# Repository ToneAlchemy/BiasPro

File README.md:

# 🎛️ Arduino Tube Amp BiasPro

This repository contains the complete, mathematically hardened firmware for a professional-grade, dual-probe vacuum tube BiasPro. Designed for guitar amplifier technicians, this tool provides real-time, high-resolution measurements of Plate Voltage, Cathode Current, and True Plate Dissipation (Watts & %) for power tubes (e.g., 6L6GC, EL34, 6V6, KT88).

This firmware was completely re-architected from scratch using modern, memory-safe embedded C++ principles to eliminate dynamic memory leaks and ensure rock-solid physical safety lockouts.

> **Current firmware version: v1.1.1** — see [CHANGE_LOG.md](CHANGE_LOG.md) for the full change history. Highlights since v1.0.0: a **vertically stacked, horizontally centered layout on the Tube Select and Profile Manager screens** (with improved line spacing for clear reading), a **Hold LEFT shortcut** to escape the Profile Manager directly to Tube Select, a **live plate-voltage readout on the Calibration screen** (match it to your DMM as you adjust), **sensor-glitch rejection** so a noisy ADC read can't false-release the lockout or flash 0 V, **profile-store protection** so a bad edit can't wipe your saved tube profiles, and a **flicker-free VOLTAGE LOCKOUT screen**.

| **1. Splash Screen** | **2. Tube Select** | **3. Live Bias Mode** |
| :---: | :---: | :---: |
|  |  |  |
| **4.  Calibration** | **5. Profiles Manager** | **6. Profile Edit** |
|  |  |  |
| **7. EDIT PROFILE** | **8. BiasPro Enclosure** | **9. BiasPro - Setup** |
|  |  |  |

---

## ⚠️ High-Voltage Safety Warning
**LETHAL VOLTAGES ARE PRESENT IN TUBE AMPLIFIERS.**

Tube amplifiers store lethal voltages in their filter capacitors even after being unplugged. This firmware is only a measurement tool; it **cannot** make unsafe wiring or handling safe. 
* Never connect the USB port to a computer while the probes are plugged into a live amplifier. 
* Always use a dummy load or speaker cabinet.
* If you are not trained in high-voltage safety, take your amplifier to a qualified technician. Build and use this project entirely at your own risk.

---

> [!CAUTION]
> ## ⚠️ WARNING: HIGH VOLTAGE SAFETY
>
> **Tube amplifiers contain lethal high voltage (often 400V–500V+), even when powered off and unplugged.**
>
> This project involves building and using test equipment that interfaces directly with these dangerous circuits.
> * **Risk of Death:** Incorrect wiring of the bias probes or misuse of this device can expose you to lethal current.
> * **Filter Capacitors:** High voltage can remain stored in the amplifier's capacitors long after the power is cut. You must know how to safely drain filter capacitors before opening any chassis.
> * **Qualified Personnel Only:** If you are not trained in high-voltage safety or are uncomfortable working with live circuits, **do not build or use this device**. Take your amplifier to a qualified technician instead.
>
> **DISCLAIMER & NO SUPPORT:** This project is provided "as is" with **no warranty and no technical support**. The author cannot provide assistance with assembly, troubleshooting, or code modifications. The author assumes no liability for injury, death, or equipment damage resulting from the use or construction of this device. **Use entirely at your own risk.**

> [!IMPORTANT]
> ### ⚡ Critical Safety: Capacitor Discharge
> Before touching any internal component or connecting probes to a chassis, you must verify the filter capacitors are drained.
>
> * **The Golden Rule:** Always measure with a multimeter to confirm 0VDC before touching anything.
> * **Discharge Tool:** Do not rely on the amp to drain itself. Use a dedicated **Capacitor Discharge Tool** to safely bleed off voltage.
>      * *DIY Tip:* You can build one using a high-wattage resistor (e.g., **2kΩ to 5kΩ, 5 Watts**) wired to a probe and an alligator clip for ground. This slows the discharge **and** prevents sparking, unlike a screwdriver short.
> * **One-Hand Rule:** When working on live amps, keep one hand in your pocket to prevent current from passing across your chest/heart.

> [!NOTE]
> ### 🛡️ Recommended Safety Gear
> If you are working inside a live amplifier chassis, we strongly recommend using the following safety equipment:
> 
> * **Isolation Transformer:** This isolates the amplifier from the mains earth ground, significantly reducing the risk of lethal shock if you accidentally touch a live component while grounded.
> * **Dim Bulb Limiter (Current Limiter):** Essential when powering up an amplifier for the first time after a repair. It prevents catastrophic damage (blown transformers) if there is a short circuit.
>      * **⚠️ CRITICAL WARNING:** Do **NOT** attempt to set the final bias while running through a Dim Bulb Limiter. The limiter drops the wall voltage, which lowers the plate voltage and gives false low bias readings. Always bypass the limiter for the final precision bias adjustment.
> * **Variac (Variable Transformer):** Highly recommended for two purposes:
>      1.  **Voltage Stabilization:** Wall voltage fluctuates. A Variac allows you to set the input voltage exactly to your country's standard (e.g., 240V in Australia, 120V in USA, 230V in UK). This ensures your bias readings are accurate and consistent, rather than drifting with high/low wall voltage.
>      2.  **Soft Start / Reforming:** Useful for slowly bringing up the voltage on vintage amplifiers to reform old capacitors safely.

> [!TIP]
> **New to Biasing?** Check out our dedicated guide:
> ### 📖 [Read the Step-by-Step Biasing Guide](BIASING_GUIDE.md)
> *Learn how to safely bias Fender Prosonic & Fixed-Bias Amps.*

---

## ⚙️ Hardware Specifications

* **MCU:** Arduino Nano / ATmega328P
* **Display:** 1.8" 128×160 ST7735/ST7735S SPI TFT (Adafruit PID 358 or compatible generic clone; see [Display Selection & Compatibility Guide](#18-tft-display-selection--compatibility-guide) below)
* **ADC:** ADS1115 (16-bit) at I2C address `0x48`
* **Inputs:** Three tactile switches (Left, Right, Center)

### Immutable Pin Map
| Function | Arduino Nano Pin |
| :--- | :--- |
| **TFT SCLK/SCL** | D13 |
| **TFT MOSI/SDA** | D11 |
| **TFT CS** | D10 |
| **TFT DC** | D9 |
| **TFT RST** | D8 |
| **Button Center** | D7 (Uses `INPUT_PULLUP`) |
| **Button Right** | D6 (Uses `INPUT_PULLUP`) |
| **Button Left** | D5 (Uses `INPUT_PULLUP`) |
| **ADS1115 SDA** | A4 |
| **ADS1115 SCL** | A5 |

### 🖥️ 1.8" TFT Display Selection & Compatibility Guide

When sourcing displays for BiasPro, you will encounter two primary hardware paths: the official Adafruit breakout or generic clone modules. Understanding their electrical architecture is essential for proper wiring and long display life:

| Feature | Adafruit 1.8" TFT Breakout (PID 358) | Generic Clone Module (`Driver IC: ST7735S` / `NOMEN_TEC`) |
| :--- | :--- | :--- |
| **Driver IC** | **ST7735R** | Usually **ST7735S** |
| **Onboard 3.3V LDO Regulator** | ✅ Yes (ultra-low-dropout 3.3V regulator) | ⚠️ **Usually present (`662K`), but verify `U1` & `J1`** |
| **Onboard Logic Level Shifter** | ✅ Yes (active CD74HC4050 buffer IC) | ❌ **None** (pins route straight to glass ribbon) |
| **5V Supply Compatibility** | ✅ Yes (accepts 3.3V – 5V on `VCC`) | ✅ Yes (if `U1` is populated and `J1` is open) |
| **5V Logic Compatibility** | ✅ Native 5V plug-and-play | ⚠️ **Requires 1kΩ to 1.5kΩ series resistors on SPI/control lines** |
| **Header Pin Labels** | `LITE, MISO, SCK, MOSI, TFT_CS, CARD_CS, D/C, RESET, VCC, Gnd` | `GND, VCC/VDD, SCL, SDA, RES/RST, DC, CS, BL/BLK` |

> [!NOTE]
> **Important Distinction on Adafruit PID 358 vs. PID 618:**  
> The official recommended reference part is the **Adafruit PID 358** assembled breakout (which includes the mounting PCB, microSD slot, 3.3V regulator, and CD74HC4050 level shifter).  
> In contrast, **Adafruit PID 618 is the raw, unmounted 1.8" TFT panel only** (flexible ribbon cable, no PCB). PID 618 is strictly 3.3V-only and requires external regulation and level shifting when paired with a 5V Arduino Nano.

---

#### Board Routing & Configuration Details

The `BiasPro_InputProtection_v3` PCB routes the global **5V** rail directly to Pin 8 (`VCC`) of the display header, and routes digital pins `D8`, `D9`, `D10`, `D11`, and `D13` straight to the display's SPI control lines without inline resistor pads. Review the configuration requirements for your specific display:

##### 1. Official Adafruit Breakout (PID 358) — *Recommended Reference Part*

The reference hardware design targets the **Adafruit PID 358** assembled breakout natively:

* **Power:** Connect `VCC` to Arduino Nano 5V (or 3.3V; the onboard regulator safely handles 3.3V–5V input) and `GND` to Arduino GND.
* **Signals:** Wire directly to the Arduino Nano with **no external resistors required** (the onboard CD74HC4050 buffer translates 5V logic down to 3.3V safely):
  * Nano `D13` → Adafruit `SCK`
  * Nano `D11` → Adafruit `MOSI`
  * Nano `D10` → Adafruit `TFT_CS`
  * Nano `D9`  → Adafruit `D/C`
  * Nano `D8`  → Adafruit `RESET`
* **Backlight:** Connect `LITE` to 3V3 or 5V (or to an Arduino PWM pin if software brightness control is desired).
* **Unused Pins:** `CARD_CS` and `MISO` belong to the onboard microSD card socket and remain unconnected in BiasPro.
* **Firmware Support:** BiasPro’s firmware uses `tft.initR(INITR_18BLACKTAB)` via the `Adafruit_ST7735` library, targeting the PID 358 natively.

---

##### 2. Generic / Chinese Clone Modules (ST7735S)

Budget 8-pin breakout modules (frequently marked *Driver IC: ST7735S* or *NOMEN_TEC V2.0*) run on native 3.3V silicon and lack active logic-level translation buffers.

* **VCC Power Compatibility (`U1` & `J1` Check):**
  * Inspect the rear PCB of the module: most clones include a 3-pin 3.3V LDO regulator marked **`662K`** (or `AMS1117-3.3`) at footprint **`U1`**, alongside an unbridged solder jumper **`J1`**.
  * If `U1` is populated and `J1` is open, feeding 5V into `VCC` is completely safe (the regulator steps 5V down to 3.3V for internal panel power).
  * **Warning:** If `U1` is unpopulated and `J1` is bridged, the module is strictly 3.3V-only. Connecting 5V to `VCC` will destroy the panel.
* **5V Logic Levels & Clamping:**
  * Because generic modules omit active buffer ICs, driving them directly with the Nano's 5V SPI lines forces the ST7735's internal silicon clamping diodes to shunt the excess voltage down to 3.3V.
  * **Intermittent Bench Biasing (Stock Direct Connection):** For standard tube biasing workflows (5 to 15 minutes of bench runtime per amplifier), the direct connection operates reliably without immediate failure.
* **Extended / Continuous Duty Cycles (Recommended Protection):** For long-term reliability and day-long bench operation, insert **1kΩ to 1.5kΩ series resistors** into every digital control line to eliminate clamping stress and keep the display controller cool:
  * Nano `D13` → [1kΩ Resistor] → Display `SCL` / `SCK`
  * Nano `D11` → [1kΩ Resistor] → Display `SDA` / `MOSI`
  * Nano `D10` → [1kΩ Resistor] → Display `CS`
  * Nano `D9`  → [1kΩ Resistor] → Display `DC` / `A0`
  * Nano `D8`  → [1kΩ Resistor] → Display `RES` / `RESET`
* **PCB Assembly Note:** Because the `BiasPro_InputProtection_v3` PCB routes the Nano directly to the display header without inline resistor pads, builders opting for series resistors should wire the clone module off-board or install inline resistors along the wiring harness rather than soldering the display directly flush into the PCB header.
* **Backlight (`BL` / `BLK`):** The onboard transistor (`Q1` / `J3Y`) and base resistor handle switching. Connect `BL` to the Nano's `3V3` pin, or to an Arduino GPIO pin through a 1kΩ resistor if software dimming is desired.

---

## 🛠️ Build & Flash Instructions

### 1. Pinned Dependencies
To guarantee a successful compile, you **must** use these exact library versions in the Arduino IDE:
* `Adafruit GFX Library` v1.12.5
* `Adafruit ST7735 and ST7789 Library` v1.11.0
* `Adafruit BusIO` v1.17.4

### 2. CRITICAL: 99% Flash Memory Limit & Bootloaders
The firmware compiles to approximately **30,626 bytes** of program storage. This is a very tight fit on older hardware, but it will successfully flash to both new and old Arduino Nanos.

* **Newer Arduino Nano (Standard Bootloader):** If you have a newer official Nano or a high-quality modern clone, use the `Processor: ATmega328P` setting in the Arduino IDE. These boards use the modern *Optiboot* bootloader, which leaves 32,256 bytes of usable flash space. The firmware will fit easily with roughly **1.6KB to spare**.

* **Older Arduino Nano & Generic Clones (Old Bootloader):** Many cheaper clones and older Nanos use the legacy bootloader, which takes up more space and leaves exactly 30,720 bytes of usable flash space. The firmware **will still successfully flash** using the `Processor: ATmega328P (Old Bootloader)` setting, fitting with roughly **94 bytes to spare**:
  ```text
  Sketch uses 30626 bytes (99%) of program storage space. Maximum is 30720 bytes.
  Global variables use 750 bytes (36%) of dynamic memory, leaving 1298 bytes for local variables. Maximum is 2048 bytes.
  ```
  It works perfectly, but you have very little room to add additional features or text without overflowing the memory.

* **Need more space on an old Nano?** You can manually upgrade an old Nano to the modern *Optiboot* bootloader using an ISP programmer. Once upgraded, you simply change your board selection in the Arduino IDE to **"Arduino Uno"** to unlock the extra 1.5KB of flash space.

### 3. EMI & I2C Freeze Protection
Tube amplifiers are electrically noisy environments. High voltage spikes, flyback EMF, or loose tube socket connections can create strong Electromagnetic Interference (EMI) that can lock up the internal I2C bus connecting the Arduino to the ADS1115 ADC.

To protect against these EMP-like events, this firmware completely bypasses the standard Adafruit ADC library and manually writes to the I2C registers. More importantly, it utilizes the modern `Wire.setWireTimeout(25000, true)` feature. 

* **How it works:** If the I2C bus freezes due to interference, the system detects the hang within 25 milliseconds, automatically resets the I2C hardware pins, and immediately resumes reading the Bias probes without ever rebooting the Arduino or losing your place on the screen.

* **Why no Hardware Watchdog Timer (WDT)?** Older versions of this project used the hardware WDT. However, a severe silicon bug in common LGT8F328P Arduino Nano clones caused the WDT to trigger infinite boot-loop crashes during UI updates. The software-level `Wire` timeout is infinitely more reliable, handles EMI elegantly, and completely avoids these bootloader bugs.

#### Hardware I²C Pull-Up Reinforcement (EMI Hardening)
In addition to the software timeout recovery, the physical BiasPro hardware reinforces the ADS1115 I²C bus with auxiliary pull-up resistors:
* **`SDA` $\rightarrow$ 4.7kΩ $\rightarrow$ `VDD`**
* **`SCL` $\rightarrow$ 4.7kΩ $\rightarrow$ `VDD`**

These $4.7\text{ k}\Omega$ metal-film resistors were added during live amplifier testing to strengthen the I²C bus against EMI-induced corruption and bus lockups in electrically aggressive valve-amplifier environments. By lowering the bus impedance and sharpening the $SDA$/$SCL$ rising edges, the bus becomes significantly more immune to capacitively coupled noise from high-voltage plate leads and transformer fields.

Many common ADS1115 breakout modules already include $10\text{ k}\Omega$ onboard pull-up resistors. Adding external $4.7\text{ k}\Omega$ resistors places them in parallel, resulting in an effective bus pull-up impedance of approximately $\approx 3.2\text{ k}\Omega$ (drawing only $\approx 1.56\text{ mA}$ sink current at 5V, comfortably within the $3\text{ mA}$ I²C standard limit). These hardware pull-ups work synergistically with the firmware’s `Wire.setWireTimeout` mechanism to deliver rock-solid stability.

---

## ⚠️ Troubleshooting

### 1. Upload Failed? (stk500 Error)
If you are unable to upload the firmware and see an error like `stk500_recv(): programmer is not responding`:

* **The Cause:** You are likely using an older Arduino Nano (or a generic clone) that uses the legacy bootloader.

* **The Fix:** In the Arduino IDE, go to **Tools > Processor** and change the setting from "ATmega328P" to **"ATmega328P (Old Bootloader)"**. Then try uploading again.
* *Note:* Newer official Nanos (and USB-C versions) usually use the standard "ATmega328P" setting.

### 2. The "Boot Loop" Issue (Legacy Hardware)
Some older Arduino Nano boards (and many low-cost clones) came with an outdated "Bootloader" that had a bug preventing the chip from recovering correctly after a hardware Watchdog Reset. 

* **The Fix:** This has been permanently fixed in this modern codebase! We completely stripped out the hardware Watchdog Timer and replaced it with a targeted `Wire.setWireTimeout` bus reset. You should no longer experience infinite boot loops when encountering EMI. If you do, ensure you have correctly installed the `Wire` library updates in the Arduino IDE.

### 3. Adafruit Display Clones ST7735 1.8" TFT - White Screen / Static / Wrong Colors?
If your display lights up but shows static, garbage pixels, or wrong colors:

* **The Cause:** You likely have a "Green Tab" or "Red Tab" clone display. The plastic tab on the screen protector often indicates the internal driver version.

* **The Fix:** Open the firmware source code (`DisplayManager.cpp` or main `.ino` configuration) and find the initialization line: `tft.initR(INITR_18BLACKTAB);` 
Change it to one of the following and re-upload until the screen looks correct:
  * `tft.initR(INITR_18GREENTAB);`
  * `tft.initR(INITR_18REDTAB);`

### 4. Arduino Nano "L" LED Flickering Constantly?
If you notice the onboard yellow/orange **`L`** LED on your Arduino Nano flickering continuously while the device is running:

* **This is completely normal and indicates healthy operation.**
* On the Arduino Nano hardware, the onboard `L` LED is hardwired directly to digital pin **`D13`**.
* In BiasPro, `D13` serves as the high-speed SPI Clock (`TftSclkPin`). Every time the live bias values update (multiple times per second), thousands of SPI clock pulses toggle D13 at high frequency.
* The flickering `L` LED effectively functions as a live hardware activity monitor showing active SPI communication between the ATmega328P and the display.

---

## 💻 Software & Development Environment

This project is written as a standard Arduino sketch (`.ino`) and was developed using the official **Arduino IDE**.

* **Recommended Method:** We strongly recommend using the **Arduino IDE** for the easiest setup. Its built-in *Library Manager* (Tools > Manage Libraries) makes it simple to install the required dependencies (e.g., Adafruit GFX) without complex manual configuration.

* **Alternative IDEs:** Advanced users can compile this code in other environments, such as **Visual Studio Code (with PlatformIO)** or **Microchip Studio**. However, please note that you will need to manually manage library paths and dependencies.
* **📥 Download Official Arduino IDE:** [Download Official Arduino IDE](https://www.arduino.cc/en/software)

---

## 🧪 Tests

The pure calculation and storage logic (bias math, probe classification, EEPROM
checksums/validation, and the over-voltage protection state machine) lives in
Arduino-independent units (`MathCalculations`, `ProtectionSystem`, `StorageCore`)
so it can be verified on a PC with any C++17 compiler — no board required. The
host tests link the **actual firmware sources**, not a copy, so they cannot drift
from what ships.

```bash
# From the repository root, with g++ (or clang++):
g++ -std=c++17 -I BiasPro test/host_calculation_tests.cpp \
    BiasPro/MathCalculations.cpp BiasPro/ProtectionSystem.cpp \
    BiasPro/StorageCore.cpp -o biaspro_host_tests
./biaspro_host_tests        # expect: "host calculation tests passed"
```

A second, source-level UI regression check (PowerShell) asserts that the display
code keeps using its incremental-redraw pattern and that the safety-screen
routing stays intact:

```powershell
powershell -ExecutionPolicy Bypass -File test/screen_redraw_static_check.ps1
```

---

## Features

BiasPro introduces professional-grade data integrity and safety features not found in standard DIY alternatives.

### 🛠 Core Functionality
* **Dual Probe Measurement:** Simultaneous real-time monitoring of Tube A and Tube B.

* **True Plate Dissipation:** Calculates power (Watts) and dissipation percentage based on the specific tube type.

* **Screen Current Correction:** Implements industry-standard math to subtract estimated screen current, ensuring the displayed bias represents true *Plate* dissipation, not just Cathode current.

### 💾 Robust Data Integrity
* **Checksum Protection:** The EEPROM data includes a computed checksum. If the memory is corrupted or a new chip is installed, the system detects the error and automatically restores safe default values, preventing dangerous behavior.

* **Safety Clamps:** The Calibration Menu now prevents users from accidentally setting dangerous values (e.g., setting a shunt resistor to 0.0Ω or a voltage scaler to 0), effectively "clamping" entries to safe, realistic ranges.

* **Profile Store Protection:** Your custom tube profiles are validated on both save and load. A malformed entry (for example a blank name) is rejected rather than written, so a bad edit can never silently wipe your saved profiles back to defaults on the next power-up.

### 🛡️ Safety & Reliability
* **Active Over-Voltage Monitor:** While in **Live Bias mode**, the plate voltage is checked on every measurement cycle; if it exceeds the configured limit the interface locks and displays a red "LOCKOUT" warning until the voltage falls back into the safe band. (The lock, once tripped, persists across screens until released.) **This automatic check runs only in Live Bias mode — it is _not_ active on the Calibration screen**, even though that screen shows a live voltage. During calibration, rely on your DMM and your own judgement (see the Calibration Guide warning below).

* **Safety Hysteresis:** The system requires a voltage drop of 50V (hysteresis) before resetting the safety lock, preventing rapid toggling near the limit.

* **Input Debouncing:** Advanced state-machine logic eliminates switch "recoil" and bounce, ensuring the cursor never jumps unintentionally.

* **Sensor-Glitch Rejection:** A failed or corrupted ADC read (for example from an EMI burst) is flagged invalid rather than trusted. An invalid reading can **never** release an active voltage lockout, and Live Bias mode holds the last good measurement instead of momentarily flashing 0 V.

* **Flicker-Free Display:** Every screen — including the red VOLTAGE LOCKOUT alert — uses incremental redraw, so critical readouts stay rock-steady instead of strobing.

* **Centered, Stacked UI Layout:** Selection screens (Tube Select and Profile Manager) feature vertically stacked, horizontally centered text elements with balanced line spacing for improved readability.

### ⚙️ On-Board Calibration
* **Software Calibration:** Shunt resistance and Voltage Divider scaling can be adjusted via the screen menu and saved to EEPROM. You do not need to edit the source code to calibrate the unit. Edits save **automatically** when you advance to the next field or leave the screen — there is no separate "save" step — which also minimises wear on the EEPROM.

* **Live Voltage Feedback:** While adjusting the Scale or Shunt fields in Calibration mode, the screen displays a live, non-blocking computed plate voltage (refreshed every ~350 ms) for the active probe. This allows you to match the calibration to your DMM readings in real time.

---

## 🧠 How It Works (Theory of Operation)

For those interested in the engineering, here is how the BiasPro safely measures high-voltage tube amplifiers.

### 1. Measuring Plate Voltage (The Voltage Divider)
The Arduino cannot measure 500V directly, and the ADS1115 is configured with a high-resolution Programmable Gain Amplifier (PGA) range of ±0.256V (256 mV) to maximize measurement accuracy.
* **The Circuit:** Inside the probe, a **Voltage Divider** network (1MΩ high-side, 100Ω low-side) scales the high voltage down to a safe millivolt range (0-256 mV).
* **The Math:** The device measures this low millivolt reading and multiplies it by the **Voltage Scale Factor** (defaults to 10.00, calibrated in software) to calculate the true High Voltage.
    * *Example:* 450V from the amp is stepped down by the 10,001:1 divider to approximately 45mV (0.045V) at the ADC input. The firmware multiplies this 45mV reading by the Scale Factor (10.00) to display "450V" on the screen.

### 2. Measuring Bias Current (The Shunt Resistor)
To measure current, we use **Ohm's Law** (`V = I × R`).
* **The Circuit:** The tube's cathode current flows through a precision **1Ω Shunt Resistor** to ground.

* **The Measurement:** The current flowing through the resistor creates a tiny voltage drop across it (e.g., 35mA of current creates 35mV).

* **The ADC:** The high-precision **ADS1115 ADC** measures this tiny voltage drop with extreme accuracy. The Arduino then converts that millivolt reading directly into milliamps (since 1mV = 1mA across a 1Ω resistor).

### 3. Calculating Dissipation (The Wattage)
Once the system knows the Voltage (V) and the Current (I), it calculates the Plate Dissipation in real-time.

* **Formula:** `Watts = Plate Voltage × Plate Current`

* **Screen Correction:** If enabled, the system first subtracts the estimated Screen Current from the total current to ensure the Wattage displayed is for the **Plate only**, providing the most accurate bias reading possible.

---

## Bill of Materials (BOM)

| Quantity | Component | Description |
| :------- | :--- | :--- |
| 1 | Arduino Nano (Recommended: USB-C Version) | Microcontroller board (ATmega328P) |
| 1 | Adafruit ST7735 1.8" TFT | 160x128 Color TFT Display (SPI) |
| 1 | ADS1115 16-Bit ADC Module | High-precision 4-channel ADC (I2C) |
| 3 | Tactile Push Buttons | Menu navigation (Left, Right, Center/Select) |
| 1 | Project Enclosure | 3D printed case (See below) |
| - | Hook-up Wire | 22 AWG for internals |
| 2 | Bias Probes | Octal (8-pin) probes (e.g., TubeDepot Bias Scout or DIY) |

* **Download Link:** [Bill of Materials (BOM) for the BiasPro.txt](./HARDWARE%20-%20PCB%20KICAD/Bill%20of%20Materials%20(BOM)%20for%20the%20BiasPro.txt)

---

## 🛑 Hardware Compatibility & Critical Warnings

Before sourcing parts, please review these critical hardware constraints to ensure your build works correctly.

### 1. ADC Module: ADS1115 Only (No ADS1015)

* **⚠️ CRITICAL:** You **MUST** use the **ADS1115 (16-Bit)** ADC module.

* **Do NOT use the ADS1015:** This is a cheaper, 12-bit version that looks identical.

* **The Issue:** The firmware uses a specific multiplier (`0.0078125 mV/bit`) calculated for 16-bit resolution. If you use an ADS1015, your bias readings will be incorrect by a factor of 16.

### 2. Display: ST7735 TFT Only (No OLEDs)

* **Required:** Adafruit **ST7735 1.8" Color TFT** (or compatible).

* **Not Supported:** This firmware is **NOT** compatible with monochrome OLED displays (SSD1306 or SH1106) used in other versions.

### 3. Arduino Nano Bootloader

* **Recommendation:** We recommend buying an Arduino Nano with the modern **Optiboot** bootloader (often found on USB-C versions) as it provides more flash memory and overall better stability.

### 4. Power Source (No Heater Power)
* **Supported:** Isolated USB Wall Charger or 9V Battery.

* **Not Supported:** Do **NOT** attempt to power this unit directly from the amplifier's 6.3V AC heater lines.

* **The Risk:** This hardware revision does not include the necessary rectification circuitry. Connecting heater lines to the Arduino will destroy the unit.

### 5. Isolation Transformers & USB

* **Clarification:** Even if you plug the amplifier into an **Isolation Transformer**, it is **STILL UNSAFE** to connect the BiasPro's USB port to a computer while probing.

* **The Physics:** Most isolation transformers pass the **Earth Ground** pin straight through. This means the Ground Loop danger persists. **Never connect USB to a PC while the probes are in an amp. If you do so, you do it at your own risk!**

### 🛠️ Building the Probes (Recommended Kit)

We highly recommend the **Tube Depot Bias Scout Kit** for your hardware. It provides a professional, safe, and robust enclosure for the socket and resistor.

* **Product Link:** [Tube Depot Bias Scout Kit](https://www.tubedepot.com/products/tubedepot-bias-scout-kit)

* **Assembly Manual:** [Download PDF Instructions](https://s3.amazonaws.com/tubedepot-com-production/spree/attached_files/td_bias_scout_assy_manual_v3.2.pdf)

**Assembly Notes for this Project:**

1. **The Resistor:** The kit includes a **1Ω 1W resistor**. This is perfect for this project and matches the default calibration (1.00Ω).

2. **Wiring Colors:** If you follow the standard instructions, the output plugs will match this project's wiring guide:
   - **Red:** Plate Voltage (Connect to PCB `V_IN` via voltage divider).
   - **Black:** Ground (Connect to PCB `GND`).
   - **White:** Cathode Current (Connect to PCB `ADC_IN`).

3. **Connection:** You can either cut the banana plugs off and wire them directly to your PCB/Enclosure, or install female banana jacks on your BiasPro enclosure for a detachable probe.

---

## 🔌 DIY Probe Construction & Theory
While we recommend the **Tube Depot Bias Scout Kit** for the easiest assembly, you can build your own probes using the Bias Scout Kit Instructions with standard components.

### 🛠️ DIY Parts List (Per Probe)
To build one probe, you will need:
* **1x Octal Tube Base:** (e.g., P-SP8-47X) - The male plug that goes into the amp.
* **1x Octal PCB Socket:** (e.g., P-ST8-810-PCL) - The female socket the tube plugs into.
* **1x 1Ω Resistor:** (2 Watt or greater, 1% Tolerance) - *Current Shunt*.
* **1x 1MΩ Resistor:** (1/2 Watt or greater, 1% Tolerance) - *Voltage Divider High Side*.
* **1x 100Ω Resistor:** (1/8 Watt or greater, 1% Tolerance) - *Voltage Divider Low Side*.
* **3-Conductor Cabling:** Shielded audio cable or twisted wire.
* **Banana Plugs / Jacks:** To connect to the main unit.
* **Assembly Manual:** [Download PDF Instructions](https://s3.amazonaws.com/tubedepot-com-production/spree/attached_files/td_bias_scout_assy_manual_v3.2.pdf)
  
> [!NOTE]
> The **Hoffman Amps Bias Checker** probe design will **NOT** work with this project. That probe only measures Cathode Current. This project requires probes that measure both Plate Voltage *and* Cathode Current.

---

## 3D Printed Enclosure

A custom enclosure has been designed to house the Arduino Nano, Display, and Buttons safely.

* **Design Platform:** TinkerCAD

* **Editable Source:** [BiasPro Enclosure V11 Files](https://www.tinkercad.com/things/gKRXVebJSTF/edit?sharecode=gUTg7qwfboPwH2RXnympp6uQYQx4FWwdrr1dFZcTKMg) *(Note: You must be logged into Tinkercad to access this link)*

* **Ready-to-Print Files:** [BiasPro_Enclosure_STL](./HARDWARE%20-%20PCB%20KICAD/BiasPro_Enclosure_STL)
  
**Printing Notes:**

You can export the `.STL` files directly from the link above. Standard PLA or PETG is suitable for this project. The case is designed to keep the low-voltage electronics isolated and secure.

---

## PCB Design & Fabrication

For a cleaner build and enhanced reliability, a custom PCB has been designed to replace hand-wiring. This board hosts the Arduino Nano, ADS1115, and input connectors.

### Key Hardware Features

* **Hardware Input Protection:** The board includes **1N4733A Zener Diodes (5.1V)** on the probe inputs. These clamp any incoming voltage spikes to ~5.1V, protecting the sensitive ADS1115 ADC from damage in case of a tube failure or surge.

* **Simplified Assembly:** Eliminates the "rat's nest" of wires common in DIY builds.

* **Fabrication Ready:** You can use the provided Gerber/KiCad files to order these boards from any fabrication house (e.g., PCBWay, JLCPCB, OSH Park).

### PCB Board Views

### PCB Board Components Views

### Schematic layout

* **Download Link:** [BiasPro - KICAD](./HARDWARE%20-%20PCB%20KICAD/BiasPro%20-%20KICAD)
  
**📥 Get KiCad Software:** [Download Official KiCad](https://www.kicad.org)

---

## Wiring / Pinout Guide

### Arduino Nano Connections
| Component | Pin Name | Nano Pin |
| :--- | :--- | :--- |
| **Buttons** | Left Button | D5 |
| | Right Button | D6 |
| | Select/Center | D7 |
| **Display (ST7735)** | CS | D10 |
| | DC (A0) | D9 |
| | RST | D8 |
| | SDA (MOSI) | D11 |
| | SCK (SCLK) | D13 |
| **ADC (ADS1115)** | SDA | A4 |
| | SCL | A5 |
| | VCC | 5V |
| | GND | GND |

### Arduino Nano Pinout 

### 🔌 Probe Wiring (Octal Sockets)

If you are building your own probes, correct wiring is essential for the math to work.
* **Pin 3 (Plate):** Connects to the Voltage Divider.
* **Pin 8 (Cathode):** Connects to the Shunt Resistor (and Ground).
* **Pin 1 & 8:** Often tied together in 6L6/EL34 amps.

*Figure: Standard Octal (8-Pin) Pinout (Bottom View).* 

---

## Powering the Device (Crucial Safety Info)

Correctly powering the Arduino Nano is critical to prevent damage to your computer, the BiasPro, or the amplifier.

### 1. Recommended: Separate USB Power Adapter

The safest way to power this device during use is with a dedicated USB wall charger (like a standard phone charger).
* **Specs:** 5V Output, at least 500mA (0.5A).

* **Connector:** Mini-USB or USB-C (for Nano).

* **⚠️ IMPORTANT - 2-Prong Only:** You must use a charger that has only **2 prongs** (ungrounded).
    * **Why?** Tube amplifiers are grounded to Earth. If you use a grounded (3-prong) power adapter for the Arduino, you may create a **Ground Loop**. This can introduce noise, cause erratic readings, or in worst-case scenarios, short high voltage to ground through your low-voltage electronics. A 2-prong adapter is "floating," which isolates the meter from Earth ground.

### 2. Battery Power (9V)

You can power the Arduino Nano via the `VIN` and `GND` pins using a 9V battery.

* **Pros:** Complete electrical isolation (100% safe from ground loops), portable, zero mains noise.
* **Cons:** The Arduino, Display, and ADC consume current constantly. A standard 9V battery may drain relatively quickly.

### 3. ⚠️ WARNING: Computer USB Port

**DO NOT** power the BiasPro from your computer's USB port while it is connected to an amplifier.

* **The Danger:** Desktop computers (and many laptops) are grounded. Connecting the USB cable ties the Arduino's Ground to the Computer's Earth Ground. Since the Probe's Ground is connected to the Amp's Ground, you create a direct Ground Loop.

* **Risk:** If a probe accident occurs or there is a voltage potential difference, high current could flow through the USB cable, destroying your computer's motherboard, the Arduino, or the amplifier.

#### When is Computer USB safe?

* **Uploads:** It is safe to connect to the computer to upload code **ONLY IF** the bias probes are **disconnected** from the amplifier.

* **Debugging:** You can use the Arduino IDE Serial Monitor (9600 baud) to confirm the firmware boots (it prints a `BiasPro Booting...` status message), but **ensure the probes are NOT connected to a live amplifier**. If you must debug a live circuit, you must use a **USB Isolator** to protect your equipment.

---

## Installation

1. **Library Dependencies:** Install the following via the Arduino IDE Library Manager:
   - `Adafruit GFX Library`
   - `Adafruit ST7735 and ST7789 Library`
   - `Adafruit BusIO`

2. **Hardware Setup:**
   - **ADS1115:** Connect via I2C (SDA -> A4, SCL -> A5).
   - **TFT Display:** Connect via SPI (Pins 8, 9, 10, 11, 13 defined in code).
   - **Buttons:** Connect to Digital Pins 5 (Left), 6 (Right), and 7 (Center/Select).

3. **Upload:** Flash the `BiasPro` firmware to your Arduino Nano.

---

## User Guide & Navigation

* **Left / Right Buttons:** Scroll through menus or adjust values.
* **Center Button (Short Click):** Select an item, confirm an edit, or advance to the next field.
* **Center Button (Long Hold):** Open the Tool Menu or return to the main screen.
* **Left Button (Long Hold / Hold LEFT):** On the Profile Manager screen, immediately return to the main Tube Select screen without selecting a profile.

### RAW SENSORS (Diagnostics Mode)
**"RAW SENSORS"** is a highly visible, dedicated diagnostics menu item located at the very end of the Tube Profile Selection carousel. It is accessed and exited using a standard short click of the center button. Selecting this profile enters a diagnostics mode that displays the raw telemetry data coming directly from the Analog-to-Digital Converter (ADC) before final mathematical conversions are applied.

* **Raw ADC Counts (e.g., `CATH: 5254`):** These are the unconverted digital integer values read directly from the ADS1115 chip. The chip measures the physical voltage and outputs a proportional number ranging from `-32768` to `+32767`.

* **Millivolts (e.g., `41.04mV`):** The system mathematically converts the raw integer count into actual millivolts (`mV`). 
   * For the **Cathode**, this millivolt reading translates directly into Milliamps (mA) due to the 1Ω shunt resistor. 
   * For the **Plate**, this millivolt reading is later multiplied by your calibrated Voltage Scale Factor to calculate the true High Voltage.

This screen is highly useful for troubleshooting probe connections, checking for ADC noise, or manually verifying the calibration math.

### Firmware Quirks (By Design)

**1. The "Invisible Spaces" in the Profile Editor**
When creating a new tube profile, the Name field holds exactly **6 characters**. If you type a short name like `6V6` (3 characters), you still have 3 invisible blank spaces remaining. 

* **The Quirk:** The system will not drop down to the "Max Watts" line until you clear all 6 slots.

* **The Solution:** Simply rapid-click the **Center** button 3 times to skip past the invisible empty spaces and move to the next line.

**2. Screen Grid Current (`Src`) is in Permille (/1000)**
To calculate True Plate Dissipation, the BiasPro subtracts the Screen Grid Current from the Cathode reading. Floating-point decimals (like 5.5%) crash the Arduino's memory limit. Therefore, the firmware uses **Permille (parts-per-thousand)**. 

* To enter a percentage, simply multiply it by 10.
* **5.5%** = enter `55` /1000
* **13.0%** = enter `130` /1000
* **4.0%** = enter `40` /1000

---

## 🧪 Safe Biasing Protocol

1. **Bench Setup:** Connect your amplifier to a speaker load or reactive load box. An Isolation Transformer and a Variac are highly recommended for stable wall-voltage readings.

2. **Probe Connection:** Ensure the amplifier is powered OFF. Remove the power tubes, insert the BiasPro probes into the amp sockets, and place the tubes into the top of the probes.

3. **Select Tube Profile:** Power on the BiasPro. Select the matching tube profile (e.g., `6L6GC`). Press Center to enter **Live Bias Mode**.

4. **Power the Amp:** Turn the amplifier ON. Wait for the tubes to warm up, then disengage standby. 

5. **Adjust Bias:** Watch the **%** and **Watts** readings. Adjust your amplifier's internal bias potentiometer until the hottest tube reaches your desired target:

   - **Cool (50% - 60%):** Maximum clean headroom, longest tube life.
   - **Warm (60% - 70%):** The "Golden Zone". Balanced harmonics and warmth.
   - **Hot (70%+):** **DANGER.** High compression, short tube life, risk of red-plating.

### Hardware Faults & Lockouts

* **HARDWARE FAULT: CHECK I2C:** The ADS1115 ADC has disconnected. The meter will permanently halt to prevent phantom voltage readings. Power cycle to reset.

* **VOLTAGE LOCKOUT:** If the probes detect a voltage spike above your configured safety limit (default 600V), the screen turns red and locks. You must wait for the voltage to drop at least 50V below the limit before the meter releases the lock. Do not attempt to bypass this.

---

## Tube Profile Manager Configuration Guide

The **Tube Profile Manager** is powerful because it allows you to customize how the meter calculates Bias for specific tube types.

### 1. Max Dissipation (Watts)
This determines the "Red Line" for your tube. The meter uses this value to calculate the **% Dissipation** displayed on the screen.

* **How to set:** Look up the "Max Plate Dissipation" in the tube's datasheet.

* **Examples (Typical Values):**
  - **EL34:** 25 Watts
  - **6L6GC:** 30 Watts
  - **6V6:** 12-14 Watts (Check your specific tube's datasheet; older types are lower).
  - **KT88 / 6550:** 35-42 Watts
* **Usage:** If you set this to 25W and measure 17.5W of dissipation, the meter will display **70%**.

### 2. Screen % Factor (Accuracy Tuning)
* **The Physics:** Standard bias probes measure **Cathode Current**, which is the sum of Plate Current + Screen Current. However, Bias should be calculated using only **Plate Current**.
* **The Solution:** The "Screen % Factor" subtracts a percentage of the total current to estimate the true Plate Current.
  - `True Plate Current = Measured Current - (Measured Current * ScreenFactor)`
* **Important (Permille Entry):** To calculate True Plate Dissipation, the BiasPro subtracts the Screen Grid Current from the Cathode reading. Floating-point decimals (like 5.5%) crash the Arduino's memory limit. Therefore, the firmware uses **Permille (parts-per-thousand)**. To enter a percentage, simply multiply it by 10.
* **Recommended Settings:**
  - **EL34:** ~13.0% -> Enter **130** (Pentodes draw more screen current).
  - **KT88 / 6550:** ~6.0% -> Enter **60** (High power beam tetrodes).
  - **6L6GC:** ~5.5% -> Enter **55** (Beam Tetrodes draw less).
  - **EL84:** ~5.0% -> Enter **50** (Miniature pentodes).
  - **6V6:** ~4.5% -> Enter **45**
  - **Raw Mode:** Set to **0** to see the raw total current without subtraction.

---

## Calibration Guide

The meter comes with **Default** calibration settings (Automatic), but for professional accuracy, we strongly recommend **Manual** calibration.

**How to Enter Calibration Mode:**
1. **From Profiles Manager:** While on the **Profiles** manager screen (accessible by holding the Center button from the main Tube Selection screen), press and hold the **Center Button** to enter Calibration Mode.
2. **Startup Shortcut:** Press and hold the **Left Button** immediately when powering on (during the splash screen) to jump straight into Calibration Mode.

### Calibration Field Ranges & Adjustments
To prevent entering invalid or dangerous values, the firmware enforces strict calibration bounds and adjustment steps:
* **Voltage Scale (on-screen: `Scale A` / `Scale B`):** Range is `5.00` to `20.00` (adjusted in steps of `0.05` via Left/Right).
* **Shunt Resistor (on-screen: `Shunt A` / `Shunt B`):** Range is `500mR` to `5000mR` (representing 0.50Ω to 5.00Ω, adjusted in steps of `10mR`). The software displays and stores this in milliohms (mR) to maintain high precision without the memory overhead of floating-point decimals.
* **Voltage Limit (on-screen: `Limit`):** Range is `300V` to `800V` (adjusted in steps of `5V`).

### Method 1: Default Calibration (Automatic)
When you first power on the device (or after a reset), it loads standard default values:
* **Voltage Scale:** Defaults to **10.00**. (Assumes standard 1MΩ/100Ω probe divider).
* **Shunt Resistor:** Defaults to **1.00**. (Assumes a perfect 1.00Ω resistor).

**Use Case:** This is "Plug and Play." It works reasonably well for standard probes, but real-world resistors often vary slightly. It is always good practice to check these settings against a multimeter anyway.

### Method 2: Manual Calibration (Precision)
For the highest accuracy, use this method to match the meter readings to a trusted Digital Multimeter (DMM).

#### A. Calibrating Voltage Scale
1. **Safety First:** Refer to your amplifier's schematic to find a safe test point for the B+ Voltage (Plate Voltage) that supplies Pin 3 of the power tubes.
2. **Connect:** With the amp powered off and drained, connect the Bias Probe to the socket.
3. **Measure:** Power on the amp. Use your DMM to measure the actual DC Voltage at the safe test point you identified.
4. **Adjust:** In the Calibration screen, step to the **"Scale A"** field (short-press Center to advance between fields).
5. **Match:** Use the Left/Right buttons to adjust the scale factor until the **"Live V"** on the screen matches the voltage shown on your DMM.
6. **Repeat** for Probe B.

> [!WARNING]
> **The over-voltage LOCKOUT alarm does _not_ run on the Calibration screen.** The automatic red-screen lockout is active **only in Live Bias mode**. During voltage-scale calibration the amp is energised and this screen shows a live "Live V" reading, but it will **not** trip the lockout if the amp faults high. Treat "Live V" as a readout only — **not** a safety alarm. Watch your DMM, keep the plate voltage within your amp's expected range, and if anything looks wrong, shut down at the amp. Once calibrated, do your actual biasing from **Live Bias mode**, where the lockout is active.

#### B. Calibrating Shunt Resistors (Bias Scout Probes)
If you are using commercial probes like the **Tube Depot Bias Scout**, they typically have three banana plugs: Red, Black, and White.
1. **Disconnect:** Remove the probes from the amplifier. The probe must be unplugged to measure resistance accurately.
2. **Identify Plugs:**
   - **Black:** Common (Ground)
   - **White:** Cathode (Current Measurement)
   - **Red:** Plate (Voltage Measurement) - *Do not use for this step.*
3. **Find DMM Lead Resistance (Critical for Accuracy):**
   - Turn your DMM to its lowest Resistance (Ω) setting.
   - Touch the Red and Black DMM probes firmly together.
   - Note the number (e.g., **0.1Ω**). This is your "Lead Resistance."
4. **Measure Probe:** Connect one DMM lead to the **Black** plug and the other to the **White** plug of the bias probe. Write down the total resistance (e.g., **1.2Ω**).
5. **Calculate True Resistance:** Subtract the Lead Resistance from the Total.
   - *Math:* `1.2Ω (Total) - 0.1Ω (Leads) = 1.1Ω (True Resistance)`
   - *Why?* For a ~1.0Ω resistor, a 0.1Ω error is huge (10%)! Not subtracting this will cause the BiasPro to calculate your current and wattage inaccurately, which could lead you to bias your amp dangerously hot.
6. **Convert to Milliohms (mR):** To preserve flash memory and avoid heavy floating-point math, the software uses milliohms (mR) for whole-number precision. Multiply your True Resistance by 1000.
   - *Math:* `1.1Ω × 1000 = 1100mR`
7. **Adjust:** In the Calibration screen, step to the **"Shunt A"** field and input your calculated milliohm value (e.g., **1100**).
8. **Repeat** for Probe B. *(Note: If your DMM reading fluctuates for a probe—for example, bouncing between 1.1Ω and 1.2Ω—you can split the difference and enter a median value like **1050** for maximum precision).*

#### C. Voltage Threshold Limiter
The **"Limit"** setting is a safety tripwire.
* **How it works:** If the probe detects a voltage higher than this setting (default 600V), the device immediately triggers a Red "DANGER" screen and locks the interface.
* **Setting it:** Set this value slightly higher than your amplifier's maximum plate voltage (e.g., if your amp runs at 450V, set the limit to 500V or 550V). This protects the meter and warns you if the amp is behaving abnormally.

#### D. Saving & Exiting
Your settings are written to EEPROM **automatically** — each time you press **Center** to advance to the next field, and again whenever you leave the screen. There is no separate "save" item to look for. To leave calibration:

* **Short-press Center** to step through the fields (Scale A → Scale B → Shunt A → Shunt B → Limit). Pressing **Center** on the last field (**Limit**) exits and returns you to the **Tube Profile Manager**.
* **Press and hold Center** at any point to jump straight back to the main **Tube Select** screen.

Either exit stores your latest values, so you can leave whichever way is convenient.

---

### 🛡️ DIY Safety Upgrade (Input Protection)
If you are building this on perfboard (instead of using the custom PCB), we strongly recommend adding input protection to save your Arduino in case of a catastrophic tube failure.
* **The Mod:** Connect a **5.1V Zener Diode** (e.g., 1N4733A) between the **ADC Input (White Wire)** and **Ground**.
* **Orientation:** The "Stripe" (Cathode) of the Zener diode must face the Signal wire; the other end goes to Ground.
* **Function:** If a tube shorts and sends high voltage down the probe line, the Zener diode will "clamp" the voltage to 5.1V, sacrificing itself to save the ADS1115 and Arduino.
*(Note: The custom PCB already includes these diodes).*

---

## 💬 Frequently Asked Questions (FAQ)

### 1. Is the BiasPro actually accurate down to four significant figures?

**Yes.** BiasPro v1.1.1 achieves and delivers this four-digit precision across all metrics (`0.1V` resolution for plate voltage and `0.1mA` for cathode current) through two key engineering upgrades:

* **High-Precision 16-Bit Telemetry:** Bypassing the stock 10-bit Arduino ADC in favor of an ADS1115 ADC managed directly via targeted I2C register commands allows for granular data capture down to a tiny `0.0078125 mV` per bit.

* **Empirical Software Calibration:** By taking measurements with a high-quality multimeter (such as a Fluke 115) and factoring out multimeter lead resistance, you can enter custom milliohm (mR) shunt values and scale factors directly into the on-board EEPROM menu. This process empirically matches the math engine to the unique physical tolerances of your probes.

### 2. Does the device monitor live tube drift?

**Yes, explicitly and dynamically.** The BiasPro is a continuous monitor designed for active bench analysis, rather than a device that merely captures a snapshot.

* **Thermal Drift Monitoring:** While running in **Live Bias** mode, the system continuously polls the ADC channels several times per second, maintaining steady readouts through flicker-free incremental redraws. This feature allows technicians to let the amplifier idle and track current drift over extended one-hour burn-in windows.

* **Active Safety Catching:** If a power tube encounters a severe failure such as thermal runaway or a structural grid short, the plate voltage or current will drift uncontrollably. BiasPro actively monitors this loop on every cycle and will instantly trip the red **VOLTAGE LOCKOUT** emergency screen to secure the workbench.

---

## Project Lineage & Acknowledgements
BiasPro is an independent clean-room rewrite of the earlier
ToneAlchemy BiasMeter project. The BiasPro firmware was re-architected
and rewritten without intentionally reusing source code from the earlier
implementations.

The broader project lineage includes:

- **ArduinoBiasMeter** by John Wagner
- **Dual Channel Arduino Bias Tester beta 14** by Kiel Lydestad
  (3DBeerGoggles)
- **ToneAlchemy BiasMeter**, which evolved from those earlier projects

The earlier projects were distributed under CC BY 4.0 and are acknowledged
here for their historical contribution to the development of the Arduino
tube-bias-meter concept.

## ⚖️ License
This project is released under the **MIT License**. See [LICENSE](LICENSE) for details.
Third-party libraries and components remain subject to their respective
licences.

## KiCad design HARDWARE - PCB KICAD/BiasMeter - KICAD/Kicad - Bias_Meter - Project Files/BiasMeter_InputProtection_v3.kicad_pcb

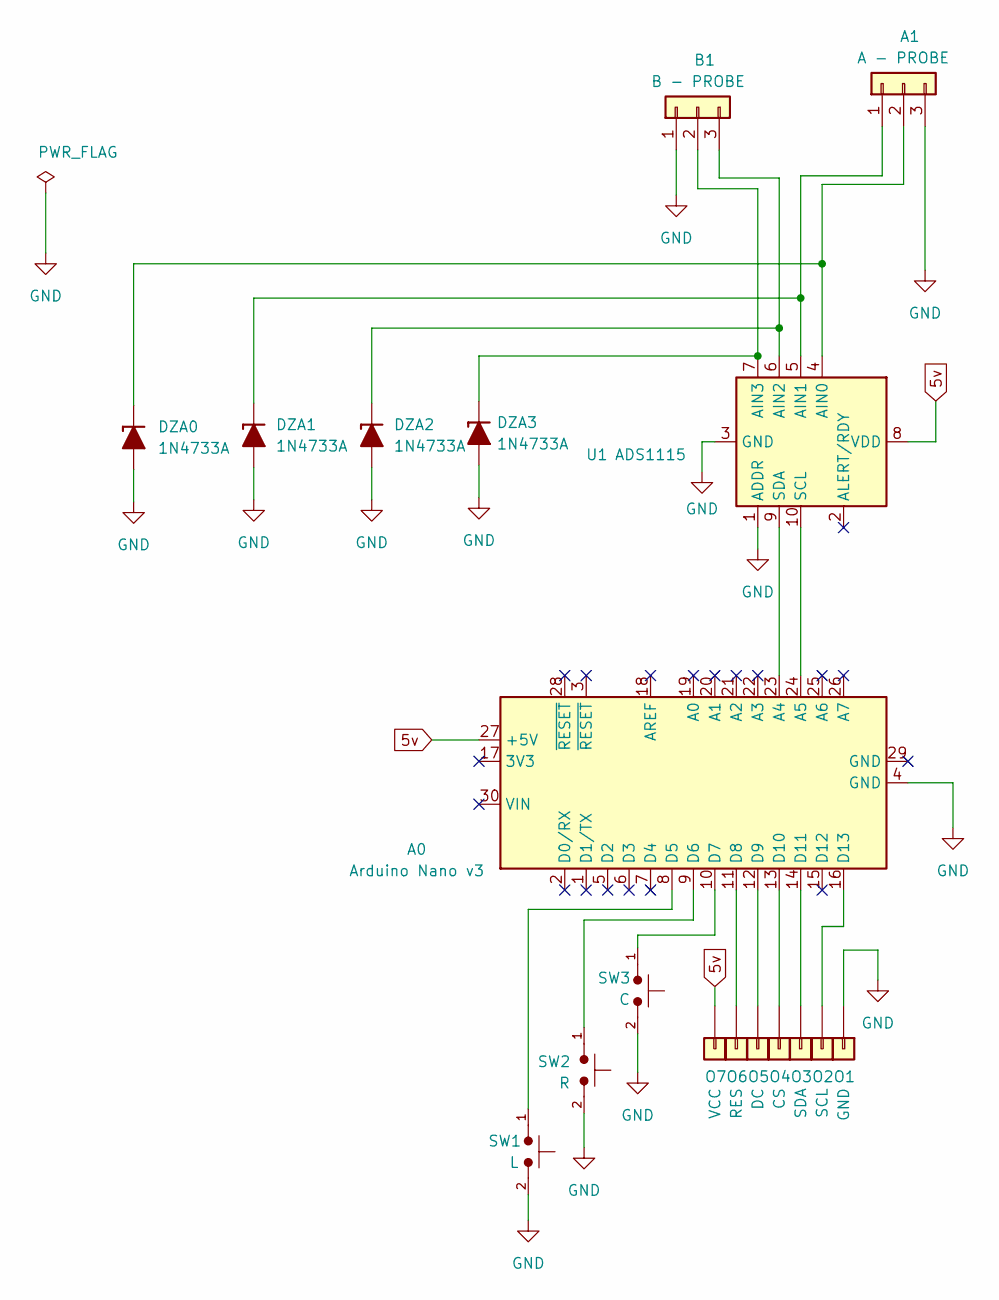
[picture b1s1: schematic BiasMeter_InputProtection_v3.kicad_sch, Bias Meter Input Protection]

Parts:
A0: Arduino Nano v3; Arduino_Nano
A1: A - PROBE; PinHeader_1x3_P2.54_Drill1.1mm
B1: B - PROBE; PinHeader_1x3_P2.54_Drill1.1mm
DZA0, DZA1, DZA2, DZA3: 1N4733A; D_DO-41_SOD81_P10.16mm_Horizontal_Zener
O1: GND; TestPoint_THTPad_D2.0mm_Drill1.0mm
O2: SCL; TestPoint_THTPad_D2.0mm_Drill1.0mm
O3: SDA; TestPoint_THTPad_D2.0mm_Drill1.0mm
O4: CS; TestPoint_THTPad_D2.0mm_Drill1.0mm
O5: DC; TestPoint_THTPad_D2.0mm_Drill1.0mm
O6: RES; TestPoint_THTPad_D2.0mm_Drill1.0mm
O7: VCC; TestPoint_THTPad_D2.0mm_Drill1.0mm
SW1: L; PinHeader_1x2_P2.54mm
SW2: R; PinHeader_1x2_P2.54mm
SW3: C; PinHeader_1x2_P2.54mm
U1: ADS1115; Adafruit_ADS1115_NEW

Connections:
5v: A0.27 (+5V), O7.1, U1.8 (VDD)
GND: A0.4 (GND), A1.3, B1.1, DZA0.2 (A), DZA1.2 (A), DZA2.2 (A), DZA3.2 (A), O1.1, SW1.2, SW2.2, SW3.2, U1.1 (ADDR), U1.3 (GND)
unnamed: A0.23 (A4), U1.9 (SDA)
unnamed: A0.24 (A5), U1.10 (SCL)
unnamed: A0.8 (D5), SW1.1
unnamed: A0.9 (D6), SW2.1
unnamed: A0.10 (D7), SW3.1
unnamed: A0.11 (D8), O6.1
unnamed: A0.12 (D9), O5.1
unnamed: A0.13 (D10), O4.1
unnamed: A0.14 (D11), O3.1
unnamed: A0.16 (D13), O2.1
unnamed: A1.1, DZA1.1 (K), U1.5 (AIN1)
unnamed: A1.2, DZA0.1 (K), U1.4 (AIN0)
unnamed: B1.2, DZA3.1 (K), U1.7 (AIN3)
unnamed: B1.3, DZA2.1 (K), U1.6 (AIN2)

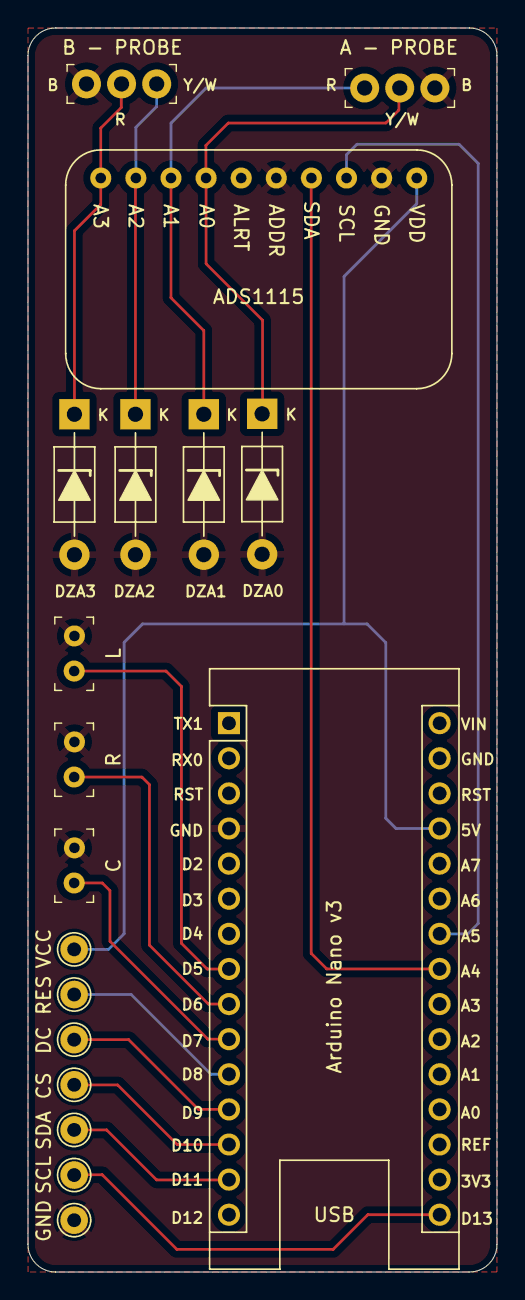
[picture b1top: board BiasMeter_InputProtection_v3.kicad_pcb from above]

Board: 2 copper layers, 33.9 x 90.0 mm, 18 parts (0 on the bottom side), 16 nets.

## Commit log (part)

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2026-06-16 udpate
2026-06-16 added new files and readme update.
2026-06-18 Updated README.md file
